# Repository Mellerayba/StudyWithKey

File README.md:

# StudyWithKey

A custom Bluetooth LE macro remote for flashcard/study-app navigation —
built from a breadboard proof-of-concept through to a battery-powered
custom PCB.

## Status
Currently halted - critical flaw in the ordered PCBs and I am not in a financial position currently to reorder them.
Firmware is completely functional and available to use freely

## Roadmap
- [x] Prototype 1 — breadboard BLE HID proof of concept
- [x] Prototype 2 — custom PCB, USB-C + battery power, hardware complete, DRC clean, ordered
- [ ] Prototype 2 — enclosure (parametric CadQuery model, pending fit check against fabricated board)
- [x] Prototype 2 — firmware (FSM-based button handling, BLE HID)
- [ ] Prototype 3 — ULP RISC-V coprocessor deep-sleep refactor

## Roadmap Update
Sadly the ordered PCB's arrived with a fatal flaw, the switches were miss oriented - causing an internal short circuit. I managed to re - solder some switches 
however it is not viable to do this for the entire order. I am not currently in the financial position to continue this project
after such a set back; however, the firmware is completely functional and available to use on any ESP-32.

## Prototypes
- [Prototype 1: Breadboard](./Physical-Prototypes/README.md) — early proof that BLE HID pairing and keypresses work end to end
- [Prototype 2: Custom PCB](./prototype-2-custom-pcb/) — purpose-built board with USB-C, LiPo charging, and a real power path
- [Physical PCB: Resoldered demo](././Physical-Prototypes/PhysicalProduct.md) — Demo photos and videos of the real custom PCB, showing that the firmware works

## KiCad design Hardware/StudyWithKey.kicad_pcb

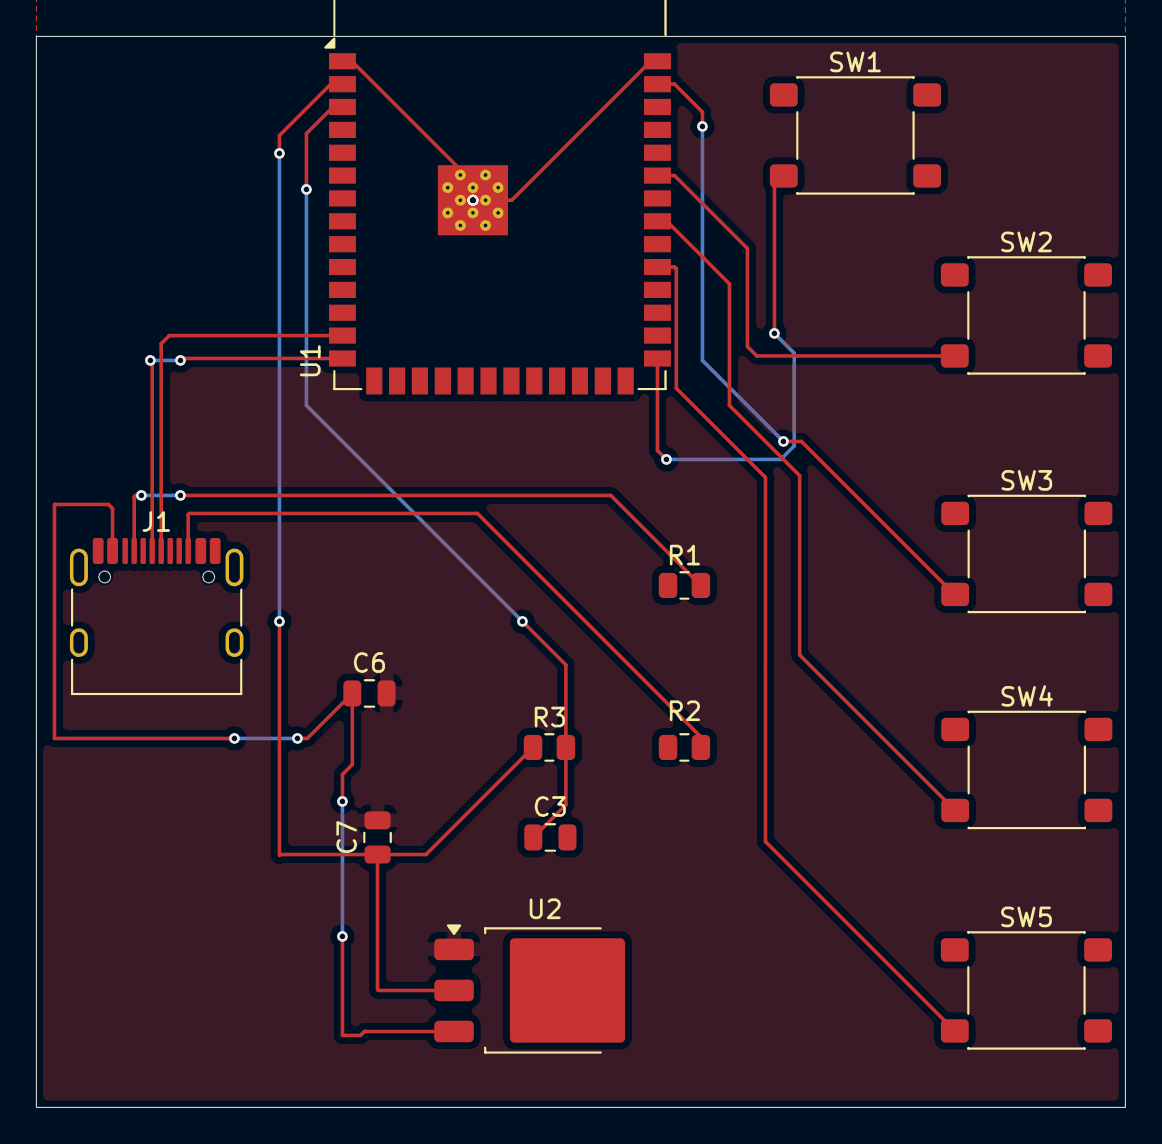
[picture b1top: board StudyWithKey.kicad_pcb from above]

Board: 2 copper layers, 60.5 x 59.5 mm, 14 parts (0 on the bottom side), 14 nets.

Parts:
C3: 1uF; C_0805_2012Metric
C6, C7: 10uF; C_0805_2012Metric
J1: USB_C_Receptacle_USB2.0_16P; USB_C_Receptacle_HRO_TYPE-C-31-M-12
R1, R2: 5.1k; R_0805_2012Metric
R3: 10k; R_0805_2012Metric
SW1, SW2, SW3, SW4, SW5: SW_Push; SW_SPST_PTS645Sx43SMTR92
U1: ESP32-S3-WROOM-1
U2: AMS1117CD-3.3; TO-252-3_TabPin2

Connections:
GND: C3.2, R1.1, R2.1, SW1.1, SW2.1, SW3.1, SW4.1, SW5.1, U1.1 (GND), U1.40 (GND), U1.41 (GND)
unnamed: J1.A5 (CC1), R1.2
unnamed: J1.B5 (CC2), R2.2
unnamed: C7.1, R3.1, U1.2 (3V3), U2.2 (VO)
unnamed: C3.1, R3.2, U1.3 (EN)
unnamed: SW1.2, U1.27 (IO0)
unnamed: SW3.2, U1.39 (IO1)
unnamed: SW5.2, U1.31 (IO38)
unnamed: SW4.2, U1.33 (IO40)
unnamed: SW2.2, U1.35 (IO42)
unnamed: J1.A6 (D+), U1.14 (USB_D+)
unnamed: J1.A7 (D-), U1.13 (USB_D-)
unnamed: C6.2, C7.2, U2.1 (GND)
unnamed: C6.1, J1.A4 (VBUS), J1.A9 (VBUS), J1.B4 (VBUS), J1.B9 (VBUS), U2.3 (VI)

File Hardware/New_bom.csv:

Designator,Footprint,Quantity,Value,LCSC Part #
C3,0805,1,1uF,
"C6, C7",0805,2,10uF,
J1,USB_C_Receptacle_HRO_TYPE-C-31-M-12,1,USB_C_Receptacle_USB2.0_16P,
"R1, R2",0805,2,5.1k,
R3,0805,1,10k,
"SW1, SW2, SW3, SW4, SW5",SW_SPST_PTS645Sx43SMTR92,5,SW_Push,
U1,ESP32-S3-WROOM-1,1,ESP32-S3-WROOM-1,
U2,TO-252-3_TabPin2,1,AMS1117CD-3.3,
